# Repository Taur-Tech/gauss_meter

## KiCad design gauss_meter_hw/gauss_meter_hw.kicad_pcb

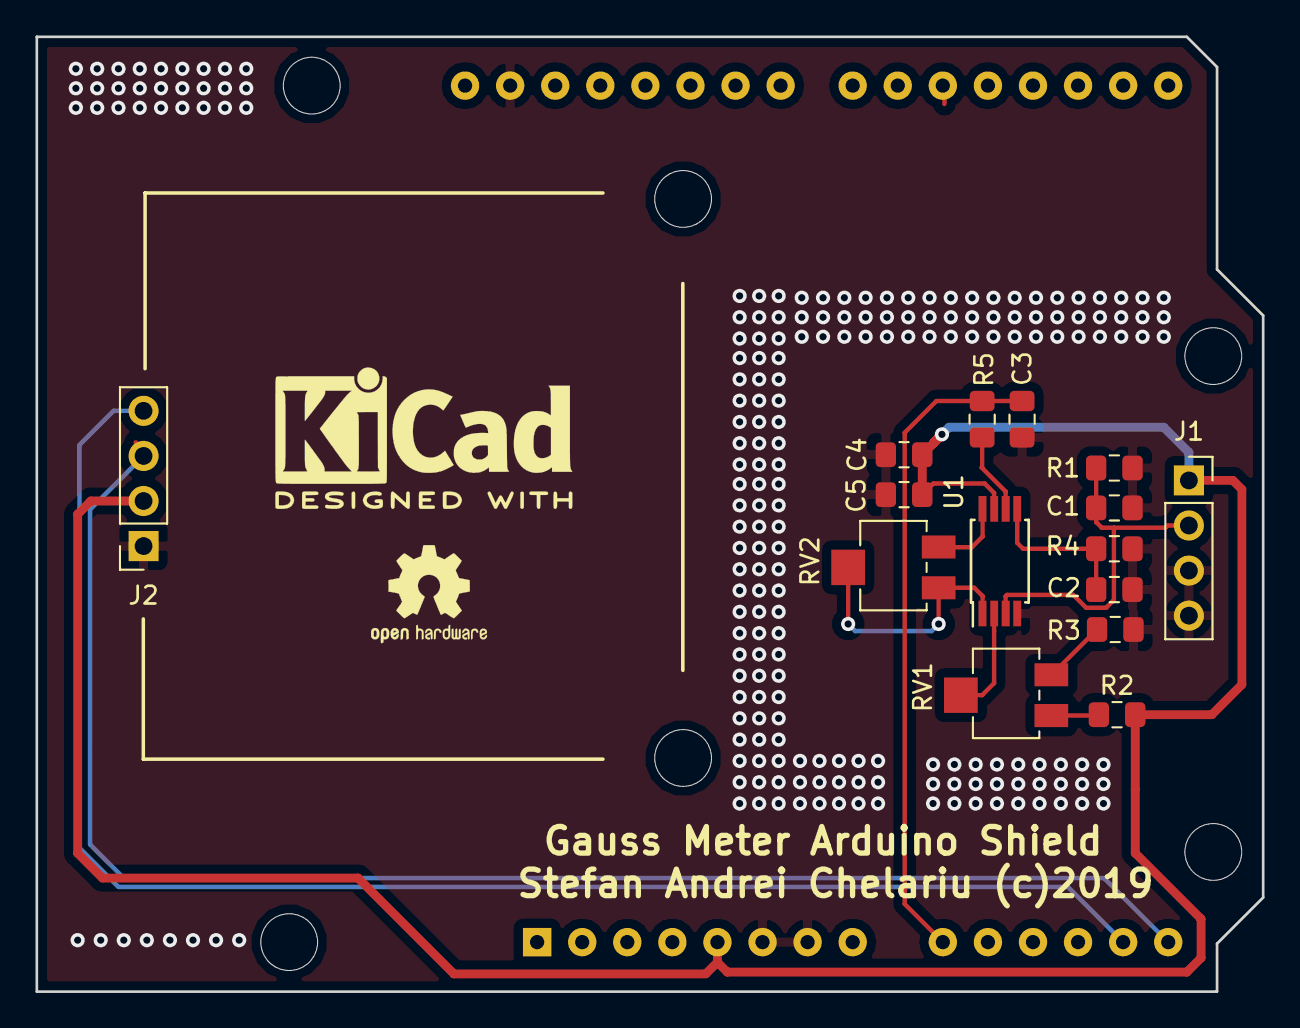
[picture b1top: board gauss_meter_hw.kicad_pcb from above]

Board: 2 copper layers, 69.1 x 53.8 mm, 16 parts (1 on the bottom side), 13 nets.

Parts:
A1: Arduino_UNO_R2; Arduino_UNO_R2_WithMountingHoles
C1: 470p; C_0805_2012Metric_Pad1.15x1.40mm_HandSolder
C2: 47p; C_0805_2012Metric_Pad1.15x1.40mm_HandSolder
C3: 1n; C_0805_2012Metric_Pad1.15x1.40mm_HandSolder
C4: 10u; C_0805_2012Metric_Pad1.15x1.40mm_HandSolder
C5: 0.1u; C_0805_2012Metric_Pad1.15x1.40mm_HandSolder
J1: Conn_01x04; PinSocket_1x04_P2.54mm_Vertical
J2: 128x64 - SSH1106; PinSocket_1x04_P2.54mm_Vertical
R1: 100k; R_0805_2012Metric_Pad1.15x1.40mm_HandSolder
R2, R3: 47k; R_0805_2012Metric_Pad1.15x1.40mm_HandSolder
R4: 10k; R_0805_2012Metric_Pad1.15x1.40mm_HandSolder
R5: 100; R_0805_2012Metric_Pad1.15x1.40mm_HandSolder
RV1, RV2: 10k; Potentiometer_Bourns_3214X_Vertical
U1: INA326; TSSOP-8_4.4x3mm_P0.65mm

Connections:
+5V: A1.5, C4.1, C5.1, J1.1, J2.2, R2.2, U1.7
GND: A1.6, A1.7, A1.29, C1.2, C2.2, C3.2, C4.2, C5.2, J1.3, J1.4, J2.1, R1.2, R3.1, R4.2, U1.4
unnamed: A1.9, C3.1, R5.1
unnamed: A1.13, J2.4
unnamed: A1.14, J2.3
unnamed: C1.1, J1.2, R1.1, U1.3
unnamed: C2.1, R4.1, U1.5
unnamed: R2.1, RV1.1
unnamed: R3.2, RV1.3
unnamed: R5.2, U1.6
unnamed: RV1.2, U1.2
unnamed: RV2.1, RV2.2, U1.1
unnamed: RV2.3, U1.8

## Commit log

2019-08-12 :space_invader: Added .gitattributes & .gitignore files
2019-08-12 Initial schematics
    Initial schematics
2019-08-13 initial PCB design
2019-09-08 revised for correct board orientation

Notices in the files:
gauss_meter_hw/gauss_meter_hw.kicad_pcb:
Stefan Andrei Chelariu (c)2019
